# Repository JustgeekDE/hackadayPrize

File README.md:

hackadayPrize
=============

All information regarding my entry for the hackaday Prize (http://hackaday.io/project/2702)

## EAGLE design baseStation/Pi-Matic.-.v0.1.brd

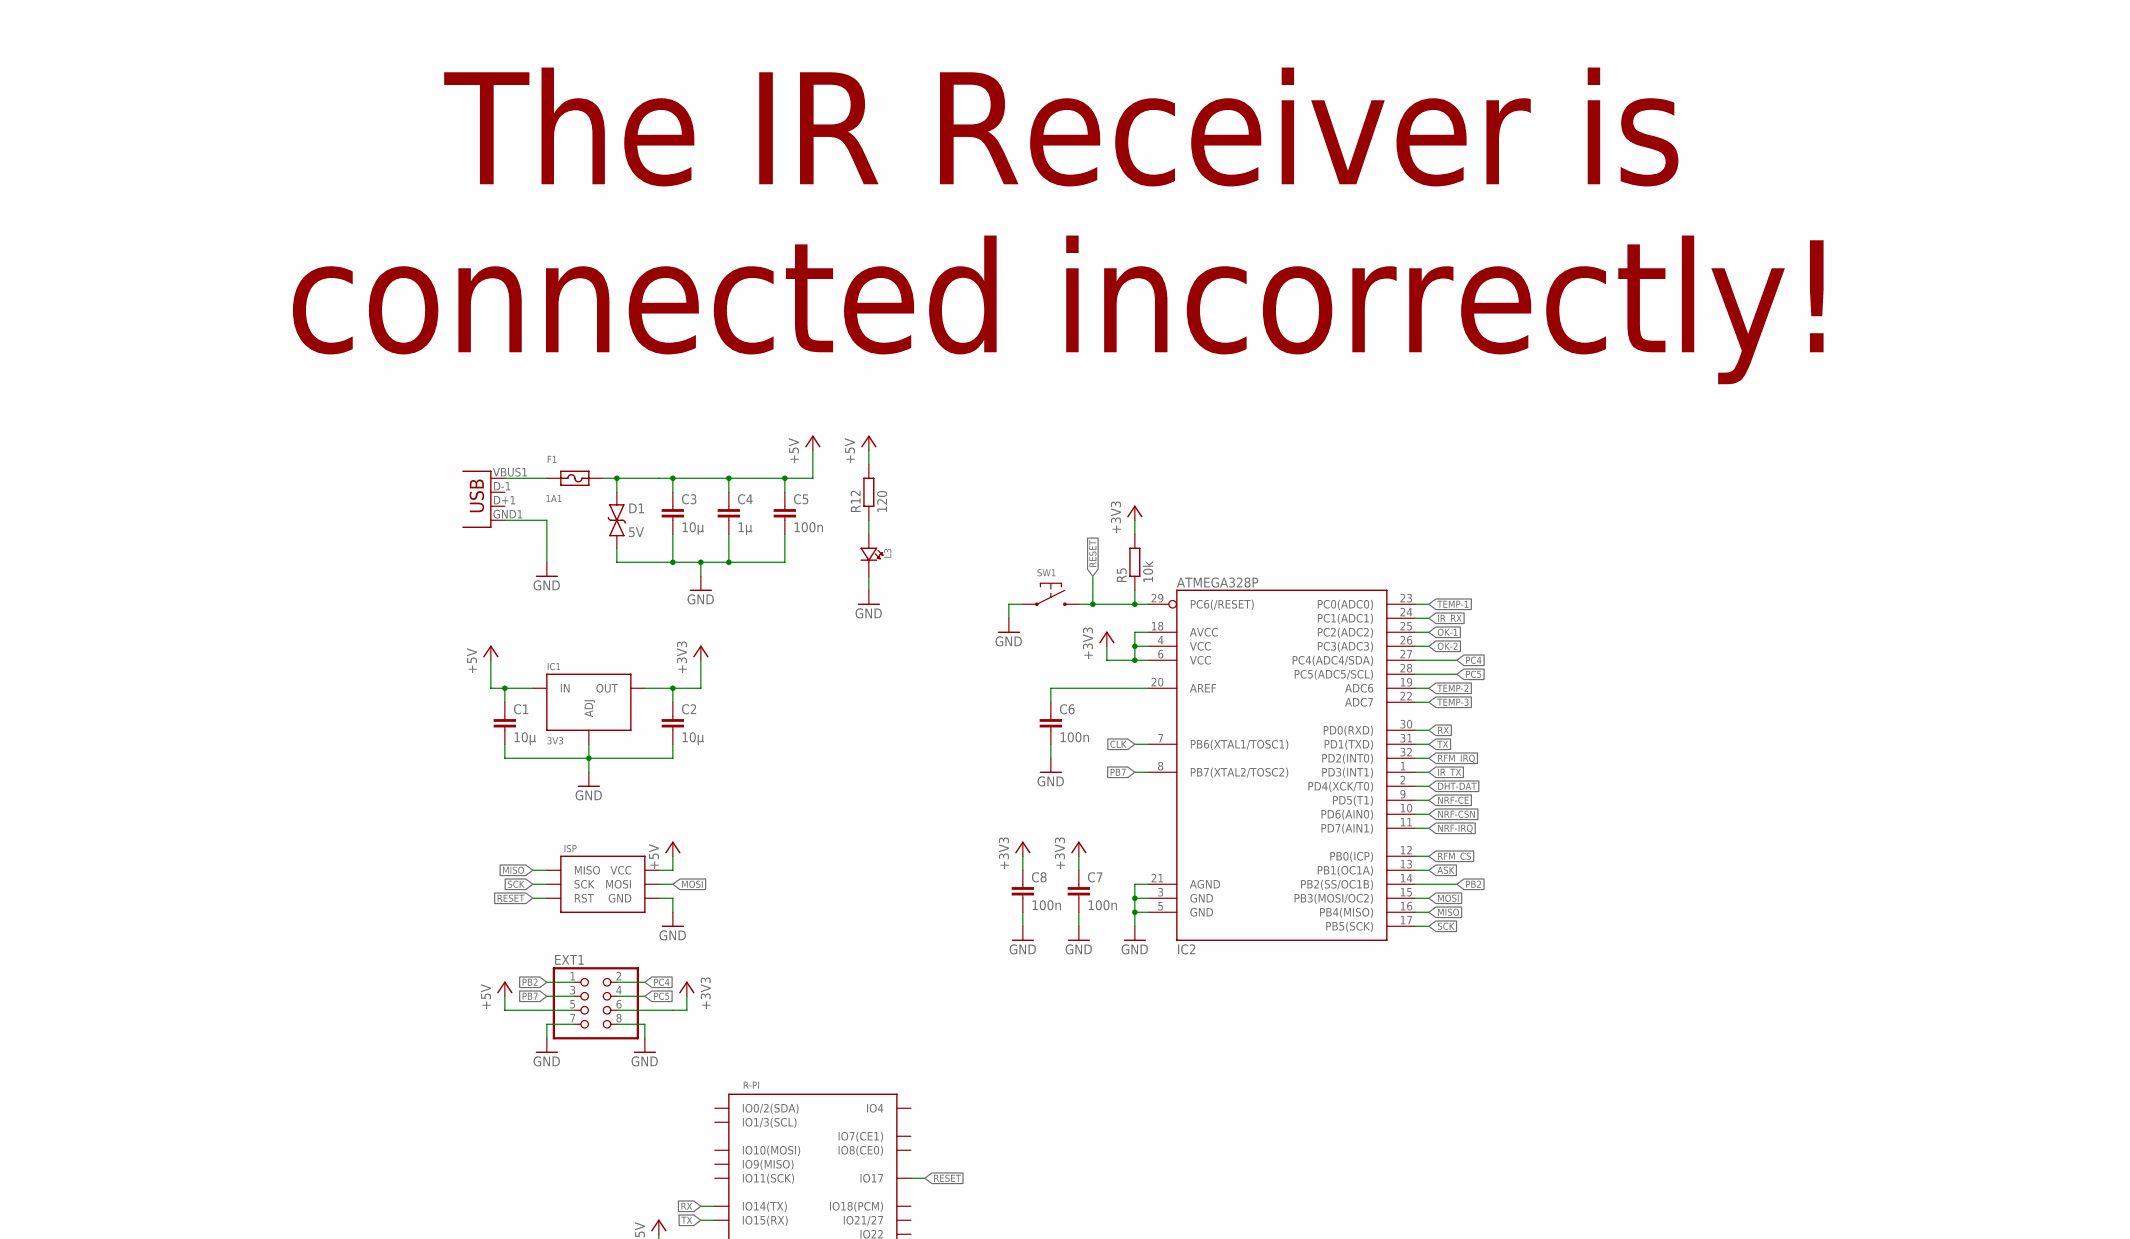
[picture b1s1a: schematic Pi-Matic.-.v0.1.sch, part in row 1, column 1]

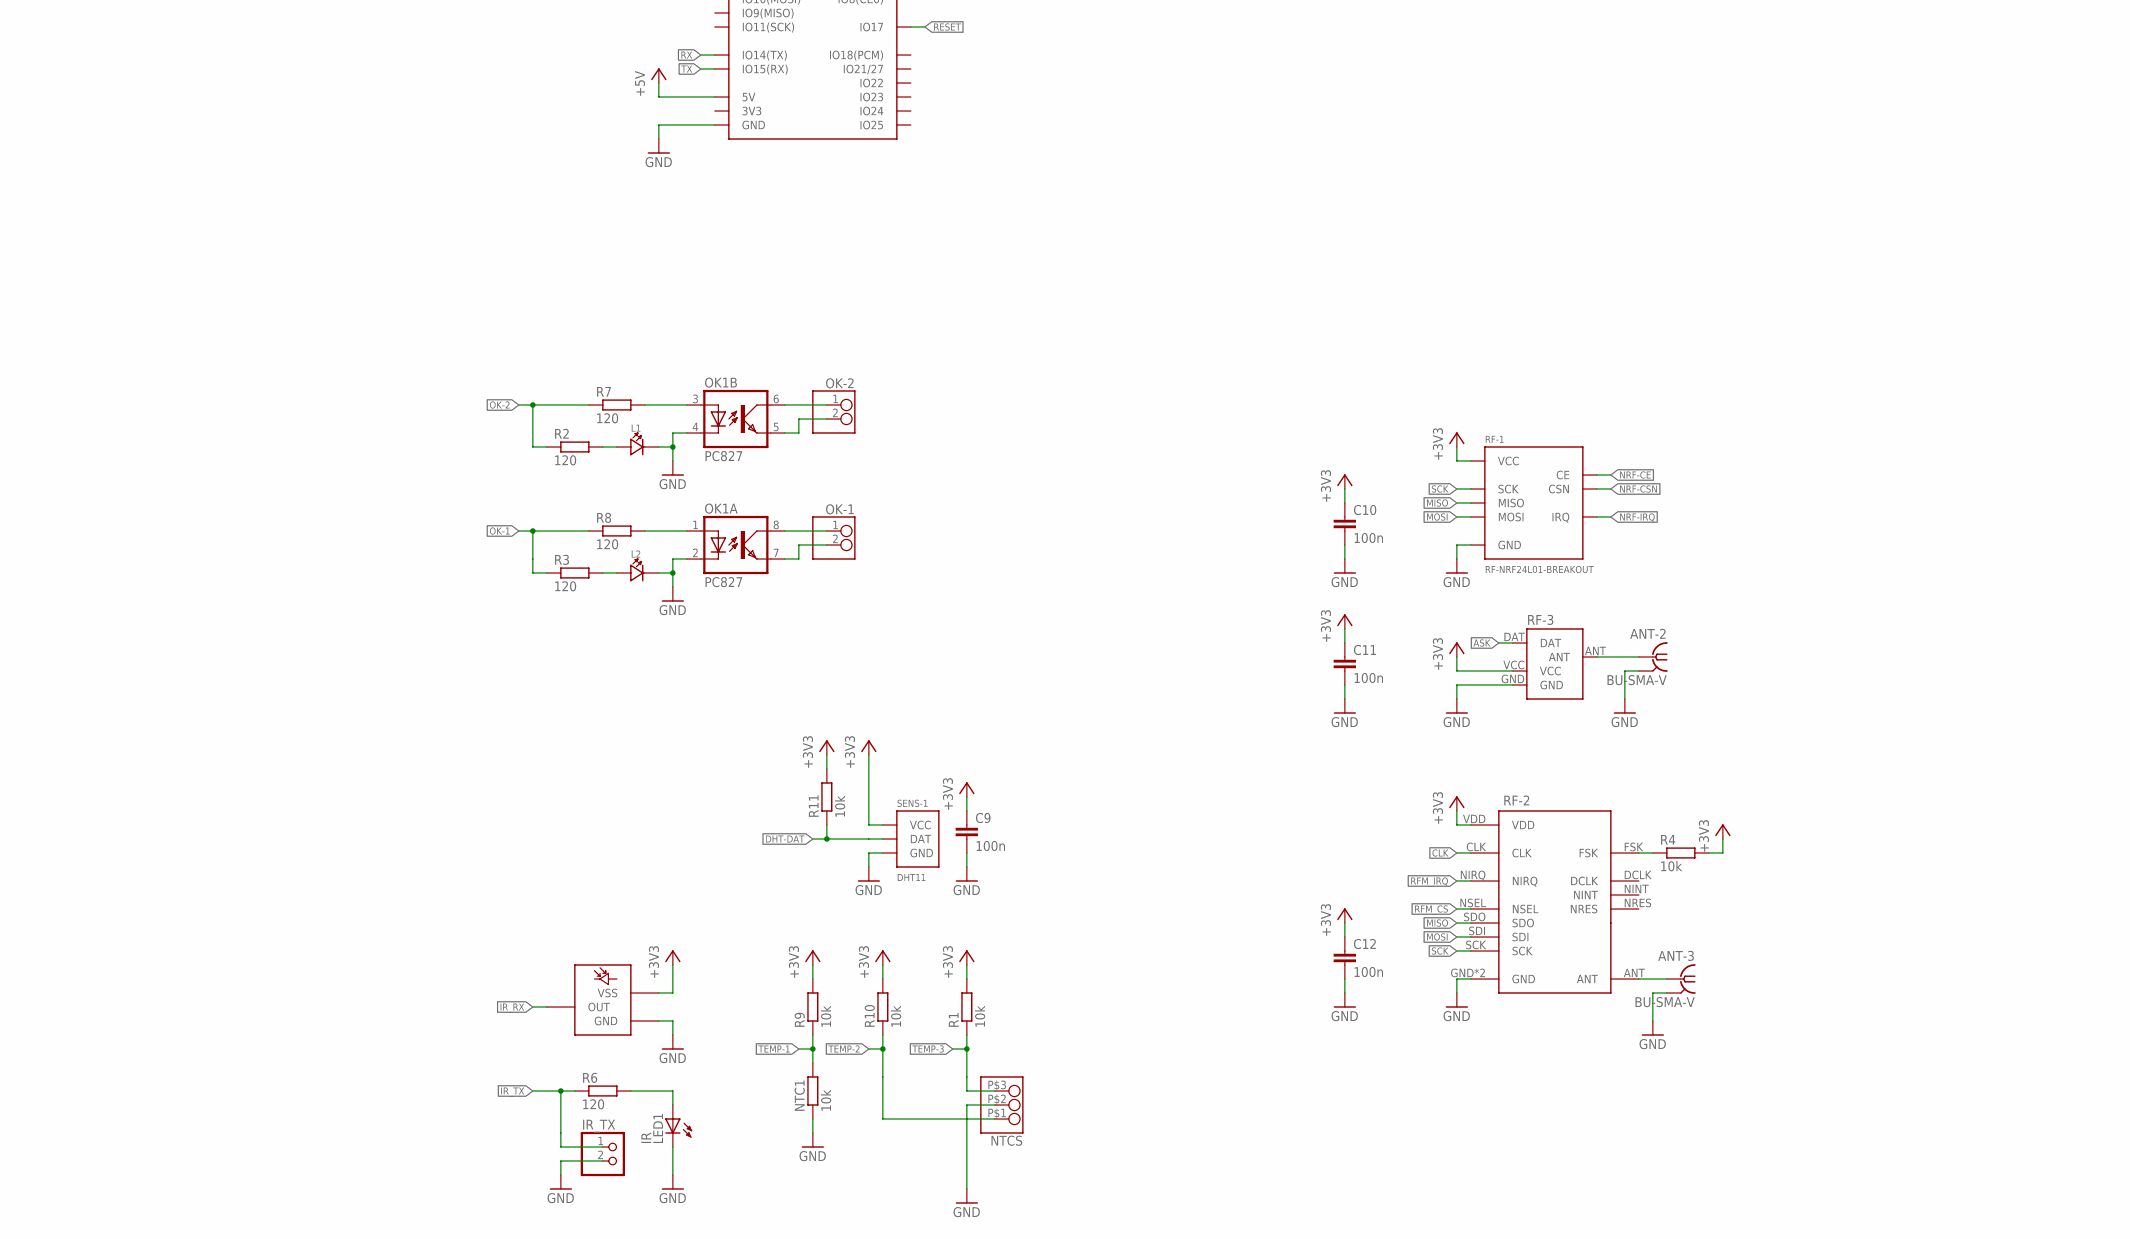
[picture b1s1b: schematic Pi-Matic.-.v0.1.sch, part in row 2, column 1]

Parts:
ANT-2, ANT-3: BU-SMA-V
C1, C2, C3: 10µ; C0805
C4: 1µ; C0805
C5, C6, C7, C8, C9, C10, C11, C12: 100n; C0603
D1: 5V; R0603
EXT1: PINHD-2X4; 2X04
F1: 1A1; SMD-1812
IC1: 3V3; SOT223
IC2: ATMEGA328P; TQFP32-08
IR_TX: PINHD-1X2/90; 1X02/90
ISP: ISP-6_PIN-NORMAL; PINHEADER-100-MIL-2X6-ISP
L1, L2, L3: LED0603; CHIPLED_0603
LED1: IR; LED5MM
NTC1: 10k; R0805
NTCS: GENERIC-1X3WAGO-5MM; WAGO-5MM-3_PIN
OK1: PC827; SMD08
OK-1, OK-2: GENERIC-1X2_PINWAGO-5MM-N; WAGO-5MM-2_PIN-1
R1, R4, R5, R9, R10, R11: 10k; R0603
R2, R3, R6, R7, R8, R12: 120; R0603
R-PI: RASPBERRY-PI
RF-1: RF-NRF24L01-BREAKOUT; RF-NRF2401
RF-2: RADIO-RFM12SMD; RADIO-RFM12-SMD
RF-3: RADIO-QAM_TX1; RADIO-ASK-QAM-TX1-SIP
SENS-1: DHT11; SENSOR-DHT11
SW1: SWITCH-DEFAULT_OFF-SMD-2_PIN; SWITCH-SMD-2_PIN-DX
U$1: IR-RECIEVERTSOP348XX; IR-REC-3PIN
U$3: USB; USB-AB-MICRO-SMD_V03

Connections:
+3V3: C2.1, C7.1, C8.1, C9.1, C10.1, C11.1, C12.1, EXT1.6, IC1.2 (OUT), IC1.4 (OUT), IC2.4 (VCC), IC2.6 (VCC), IC2.18 (AVCC), R1.2, R4.2, R5.2, R9.2, R10.2, R11.2, RF-1.P$2 (VCC), RF-2.VDD, RF-3.VCC, SENS-1.P$1 (VCC), U$1.P$3 (VSS)
+5V: C1.1, C3.1, C4.1, C5.1, D1.1, EXT1.5, F1.P$2, IC1.3 (IN), ISP.P$6 (VCC), R12.2, R-PI.2 (5V), R-PI.4 (5V)
ASK: IC2.13 (PB1(OC1A)), RF-3.DAT
CLK: IC2.7 (PB6(XTAL1/TOSC1)), RF-2.CLK
DHT-DAT: IC2.2 (PD4(XCK/T0)), R11.1, SENS-1.P$2 (DAT)
GND: ANT-2.2, ANT-2.3 (2), ANT-2.4 (2), ANT-2.5 (2), ANT-3.2, ANT-3.3 (2), ANT-3.4 (2), ANT-3.5 (2), C1.2, C2.2, C3.2, C4.2, C5.2, C6.2, C7.2, C8.2, C9.2, C10.2, C11.2, C12.2, D1.2, EXT1.7, EXT1.8, IC1.1 (ADJ), IC2.3 (GND), IC2.5 (GND), IC2.21 (AGND), IR_TX.2, ISP.P$4 (GND), L1.C, L2.C, L3.C, LED1.K (C), NTC1.1, NTCS.P$2 (2), OK1.2 (C), OK1.4 (C), R-PI.6 (GND), R-PI.9 (GND), R-PI.14 (GND), R-PI.20 (GND), R-PI.25 (GND), RF-1.P$1 (GND), RF-2.GND, RF-2.GND_ (GND), RF-3.GND, SENS-1.P$4 (GND), SW1.P$1, U$1.P$2 (GND), U$3.GND1 (GND)
IR_RX: IC2.24 (PC1(ADC1)), U$1.P$1 (OUT)
IR_TX: IC2.1 (PD3(INT1)), IR_TX.1, R6.1
MISO: IC2.16 (PB4(MISO)), ISP.P$1 (MISO), RF-1.P$7 (MISO), RF-2.SDO
MOSI: IC2.15 (PB3(MOSI/OC2)), ISP.P$5 (MOSI), RF-1.P$6 (MOSI), RF-2.SDI
unnamed: ANT-2.1, RF-3.ANT
unnamed: ANT-3.1, RF-2.ANT
unnamed: LED1.A, R6.2
unnamed: R4.1, RF-2.FSK
unnamed: OK1.1 (A), R8.2
unnamed: OK1.3 (A), R7.2
unnamed: OK1.5 (EMIT), OK-2.2
unnamed: OK1.6 (COL), OK-2.1
unnamed: OK1.8 (COL), OK-1.1
unnamed: OK1.7 (EMIT), OK-1.2
unnamed: L1.A, R2.2
unnamed: L2.A, R3.2
unnamed: F1.P$1, U$3.VBUS1 (VBUS)
unnamed: L3.A, R12.1
unnamed: C6.1, IC2.20 (AREF)
NRF-CE: IC2.9 (PD5(T1)), RF-1.P$3 (CE)
NRF-CSN: IC2.10 (PD6(AIN0)), RF-1.P$4 (CSN)
NRF-IRQ: IC2.11 (PD7(AIN1)), RF-1.P$8 (IRQ)
OK-1: IC2.25 (PC2(ADC2)), R3.1, R8.1
OK-2: IC2.26 (PC3(ADC3)), R2.1, R7.1
PB2: EXT1.1, IC2.14 (PB2(SS/OC1B))
PB7: EXT1.3, IC2.8 (PB7(XTAL2/TOSC2))
PC4: EXT1.2, IC2.27 (PC4(ADC4/SDA))
PC5: EXT1.4, IC2.28 (PC5(ADC5/SCL))
RESET: IC2.29 (PC6(/RESET)), ISP.P$3 (RST), R5.1, R-PI.11 (IO17), SW1.P$2
RFM_CS: IC2.12 (PB0(ICP)), RF-2.NSEL
RFM_IRQ: IC2.32 (PD2(INT0)), RF-2.NIRQ
RX: IC2.30 (PD0(RXD)), R-PI.8 (IO14(TX))
SCK: IC2.17 (PB5(SCK)), ISP.P$2 (SCK), RF-1.P$5 (SCK), RF-2.SCK
TEMP-1: IC2.23 (PC0(ADC0)), NTC1.2, R9.1
TEMP-2: IC2.19 (ADC6), NTCS.P$1 (1), R10.1
TEMP-3: IC2.22 (ADC7), NTCS.P$3 (3), R1.1
TX: IC2.31 (PD1(TXD)), R-PI.10 (IO15(RX))

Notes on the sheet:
The IR Receiver is connected incorrectly!

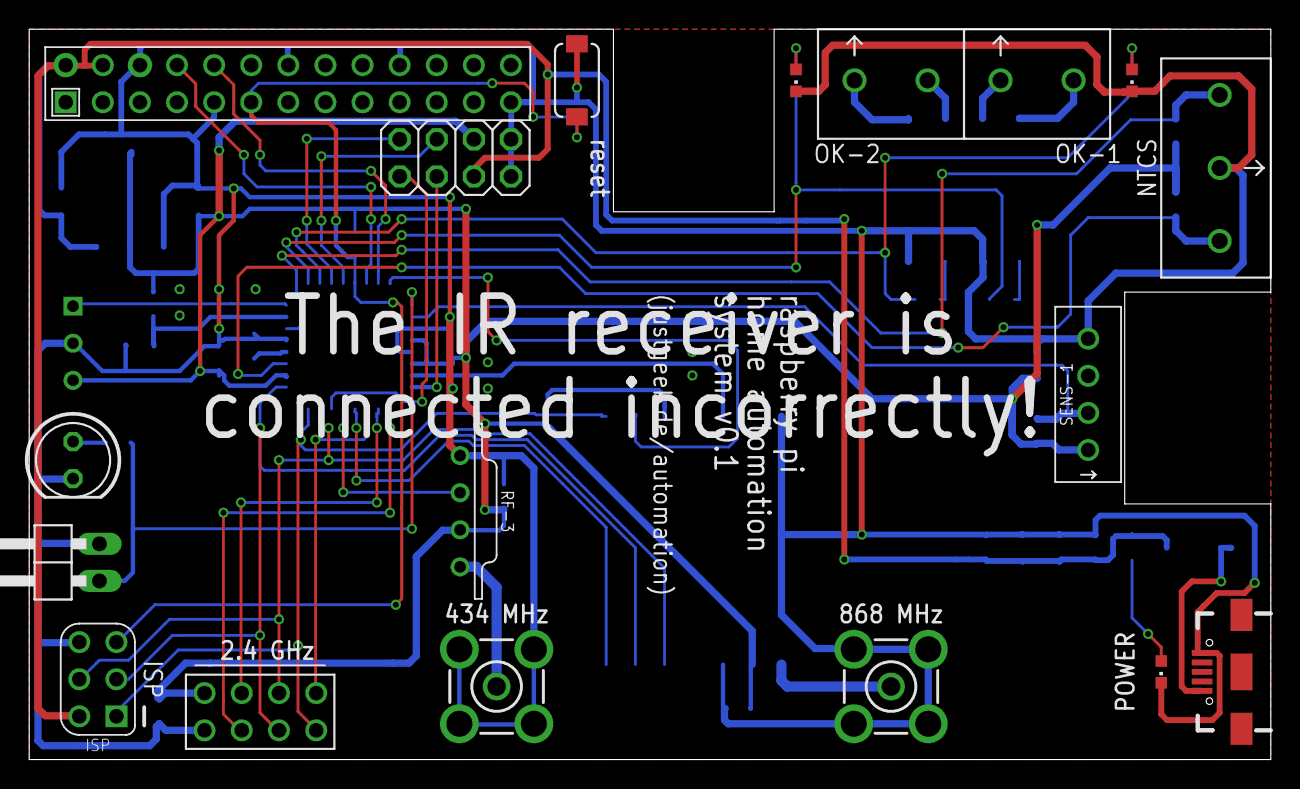
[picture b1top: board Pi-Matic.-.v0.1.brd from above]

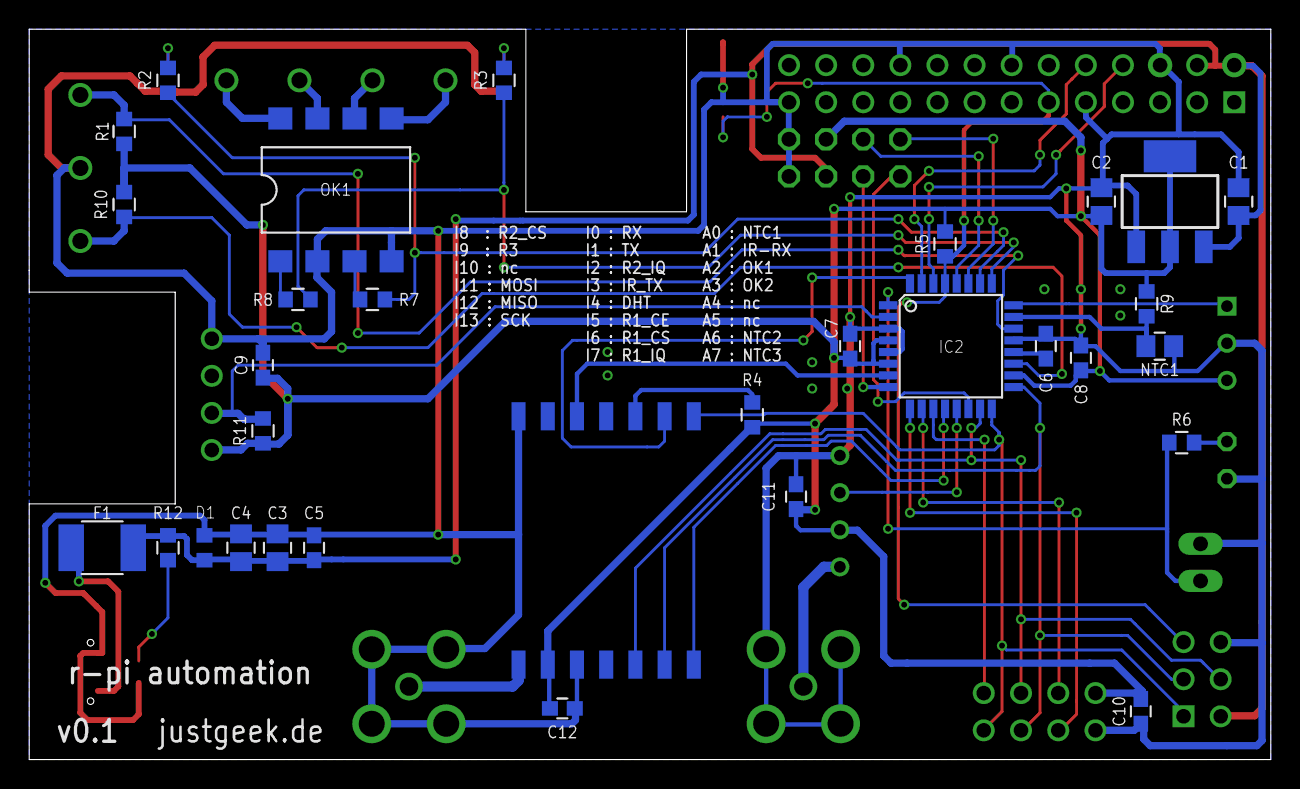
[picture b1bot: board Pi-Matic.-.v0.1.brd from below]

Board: 2 copper layers, 85.0 x 50.0 mm, 51 parts (31 on the bottom side), 43 nets.

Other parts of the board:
U$2: LOGO-JUSTGEEK-XS-MASK

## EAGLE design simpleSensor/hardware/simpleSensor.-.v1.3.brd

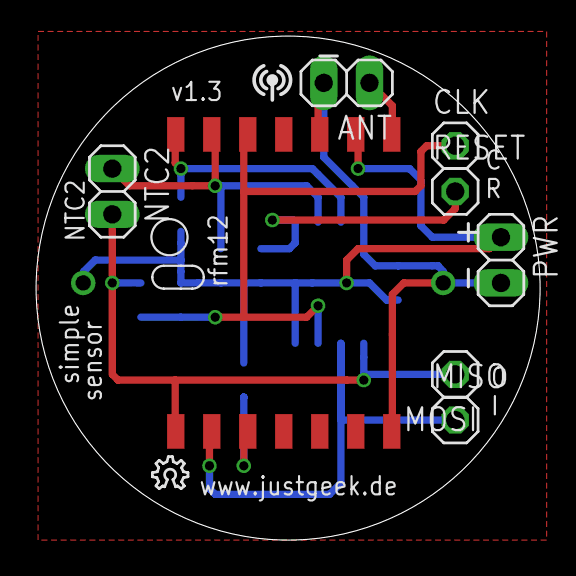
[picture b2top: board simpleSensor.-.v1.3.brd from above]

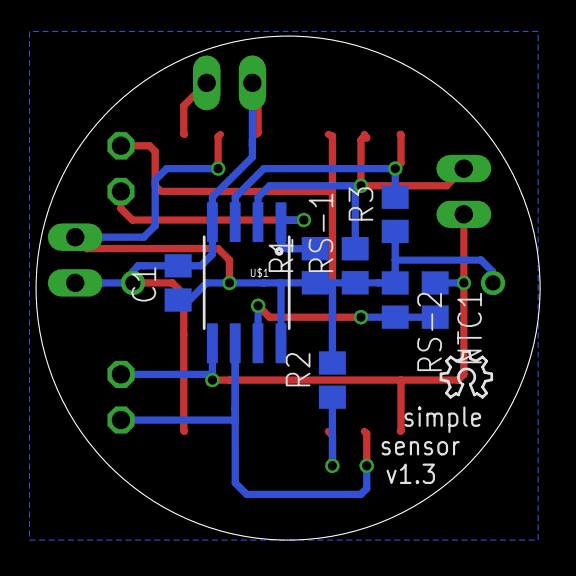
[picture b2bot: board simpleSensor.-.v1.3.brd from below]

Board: 2 copper layers, 28.0 x 28.0 mm, 19 parts (10 on the bottom side), 10 nets.

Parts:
ANT: 1X02
BAT: CR2032; BATTERY_2032_HOR
C1: 100n; C0805
CLK: 1X01
MISO: 1X01
MOSI: 1X01
NTC1: 10k; R0805
NTC2: 1X02
PWR: 1X02
R1, R2, R3: 10k; R0805
RESET: 1X01
RFM12: RFM12SMD; RFM_SMD
RS-1, RS-2: 10k; R0805
U$1: ATTINY45; SO08-EIAJ
U$2: OSHW_6X70_NOTEXT
U$3: OSHW_6X100_NOTEXT

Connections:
ANT: ANT.1, RFM12.ANT
GND: ANT.2, BAT.VSS, C1.2, PWR.2, RFM12.GND, RFM12.GND_, U$1.4
unnamed: R2.1, RFM12.FSK
PB0: MOSI.1, NTC1.1, NTC2.2, RFM12.SDO, U$1.5
PB1: MISO.1, RFM12.NIRQ, U$1.6
PB2: CLK.1, NTC1.2, RFM12.SDI, RS-2.2, U$1.7
PB3: NTC2.1, RFM12.SCK, RS-1.2, U$1.2
PB4: R3.2, RFM12.NSEL, U$1.3
RESET: R1.2, RESET.1, U$1.1
VCC: BAT.VCC, C1.1, PWR.1, R1.1, R2.2, R3.1, RFM12.VDD, RS-1.1, RS-2.1, U$1.8

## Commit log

2014-08-20 Initial check-in
2014-08-20 Old version
    Old version of the base station for documentation purposes

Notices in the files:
parts and their libraries:
SparkFun-DigitalIC: Licensing: Creative Commons ShareAlike 4.0 International - https://creativecommons.org/licenses/by-sa/4.0
